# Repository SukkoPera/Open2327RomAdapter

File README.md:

# Open2327RomAdapter
Open2327RomAdapter is an Open Hardware adapter PCB that allows the use of a 27xxx EPROM in place of a 2364 and other PROMs. This is mainly useful for replacing the KERNAL and other ROMs in VIC-20 and Commodore 64 home computers and 1541 drives.

## Summary
The KERNAL ROM in a Commodore 64 is a 2364 model (8 KB), which comes in a 24-pin package. In some cases it is necessary to replace it, but 24-pin EPROMs are not easily available. Besides, in some cases you want to have multiple KERNAL ROMs that you can select with a switch (think about [JiffyDOS](http://www.go4retro.com/products/jiffydos/)).

Open2327RomAdapter comes as an adapter PCB that sits inbetween the original socket and the new chip and solves both those problems, by allowing the use of 28-pin EPROMs, which are cheaper and much more common. It also allows the use of EPROMs bigger than the original ROM, with solder pads where switches can be wired to allow the selection of a particular ROM.

## Assembly
1. Solder the R1-R3 0805 SMD resistors first (Note: do NOT install R4, see below). My suggested technique is as follows: put a small blob of solder on one of the pads, then grab a resistor with tweezers, reheat the solder and slide the resistor into it, keeping it flat on the board. Hold it in place with your tweezers and take the iron away. If you didn't place it straight, reheat and correct with the tweezers. Finally solder the other end. It's not that hard, you just need to practice a few times.
1. Put the pin headers into a solderless breadboard and lay the board on them, with the 0805 resistors facing down (i.e.: you should not see them). Make sure to use the two shortest hole series. Solder into place.
1. Remove the board from the solderless breadboard. Using flush cutters, cut the top two pins on the right (on the soldering side) so that they are as flush to the board as possible. Repeat with the bottom two pins. Take the socket and do a test fit, it should sit flush to the board.
1. Turn the board over and solder down the socket. Again, make sure it sits as flush as possible.
1. You are done! Try to fit the adapter in the socket on your board or solder it down, if you prefer. In both cases, you can trim the pins shorter if you need.

## Installation
Open2327RomAdapter has been designed with a Winbond W27C512 EEPROM in mind (and W27*E*512 should work just as well). This is a 64 KB chip (thus it can hold up to 8 ROM images, more than enough for most needs), which is widely available, cheap and electrically erasable, which avoids the need for a clunky UV-eraser. **This is the only part that was thoroughly tested**.

Three 0805 SMD resistors must be soldered to the bottom side of the board, according to the following table:

| (E)EPROM | Size  | # of images |  R1  |  R2  |  R3  | Switchable pads |
|----------|-------|-------------|------|------|------|-----------------|
| 2764     | 8 KB  | 1           | 0R   | 0R   | 0R   | -               |
| 27128    | 16 KB | 2           | 10k  | 0R   | 0R   | A13             |
| 27256    | 32 KB | 4           | 10k  | 10k  | 0R   | A13, A14        |
| 27512*   | 64 KB | 8           | 10k  | 10k  | 10k  | A13, A14, A15   |

\* This is the only configuration that has been tested. **USE OTHER CONFIGURATIONS AT YOUR RISK!**

Note that `0R` means that you have to install a 0-ohm resistor. Alternatively you can bridge the pads with a solder blob, but don't leave the spot empty. Where the recommended value is `10k`, instead, you have some flexibility: probably any value between 5k and 100k will do.

When flashing the (E)EPROM, make sure that every file is exactly 8192 bytes long and just concatenate them. You don't need to use all of the available space, but keep in mind that the unused address lines are pulled high. This means that if you use a 27512 EPROM with a single image and no switches, for instance, the image must be flashed at $E000 (i.e.: as if it was the last of 8 concatenated images).

The adapter has been carefully sized to fit both inside a VIC-20 (tested on the KERNAL and BASIC ROMs on an Assy #250403 board) C64 (tested on the KERNAL of an Assy #250425 board) and a 1541 drive. It can usually be installed in the original ROM socket, with no need to desolder it.

To switch between ROMs, you will need one or more switches. Every switch must connect one of the A13-A15 pads to ground when enabled. A ground pad is available on the board, but any ground spot on the C64 board can be used as well, if easier to reach. Since having more than switch can be cumbersome, a rotary switch can be used as well.

### Replacing 2332 ROMs
2332 ROMs only hold 4 Kb of data. This means that you can switch among even more ROM images if you use a bigger EPROM. In order to do this, you will need to free the A12 address line, which requires a few extra steps:
1. Solder a 10k resistor at R4.
1. Cut the JP1 jumper open.
1. Solder another switch between the A12 pad on the bottom of the board and ground.

**IMPORTANT: ALWAYS TURN YOUR C64 OFF BEFORE MOVING THE ROM SELECTION SWITCH(ES).**

## License
The Open2327RomAdapter documentation, including the design itself, is copyright &copy; SukkoPera 2017-2020.

Open2327RomAdapter is Open Hardware licensed under the [CERN OHL v. 1.2](http://ohwr.org/cernohl).

You may redistribute and modify this documentation under the terms of the CERN OHL v.1.2. This documentation is distributed *as is* and WITHOUT ANY EXPRESS OR IMPLIED WARRANTIES whatsoever with respect to its functionality, operability or use, including, without limitation, any implied warranties OF MERCHANTABILITY, SATISFACTORY QUALITY, FITNESS FOR A PARTICULAR PURPOSE or infringement. We expressly disclaim any liability whatsoever for any direct, indirect, consequential, incidental or special damages, including, without limitation, lost revenues, lost profits, losses resulting from business interruption or loss of data, regardless of the form of action or legal theory under which the liability may be asserted, even if advised of the possibility or likelihood of such damages.

A copy of the full license is included in file [LICENSE.pdf](LICENSE.pdf), please refer to it for applicable conditions. In order to properly deal with its terms, please see file [LICENSE_HOWTO.pdf](LICENSE_HOWTO.pdf).

The contact points for information about manufactured Products (see section 4.2) are listed in file [PRODUCT.md](PRODUCT.md).

Any modifications made by Licensees (see section 3.4.b) shall be recorded in file [CHANGES.md](CHANGES.md).

The Documentation Location of the original project is https://github.com/SukkoPera/Open2327RomAdapter/.

## Support the Project
If you want to support the project, you can order the boards from PCBWay through this link:

You get my gratitude and cheap, professionally-made and good quality PCBs, I get some credit that will help with this and [other projects](https://www.pcbway.com/project/member/shareproject/?bmbid=41100). You won't even have to worry about the various PCB options, it's all pre-configured for you!

Also, if you still have to register to that site, [you can use this link](https://www.pcbway.com/setinvite.aspx?inviteid=41100) to get some bonus initial credit (and yield me some more).

You can also buy me a coffee if you want:

## Get Support
If you need help or have questions, you can join [the official Telegram group](https://t.me/joinchat/HUHdWBC9J9JnYIrvTYfZmg).

## Thanks
The following links were useful during the development of this project:
- https://ist.uwaterloo.ca/~schepers/roms.html
- https://ist.uwaterloo.ca/~schepers/sockets.html
- http://smisioto.no-ip.org/elettronica/kicad/kicad.htm

The following people contributed work:
- Andre Miller helped with the testing.
- Tim Abraham suggested and tested the A12 hack.

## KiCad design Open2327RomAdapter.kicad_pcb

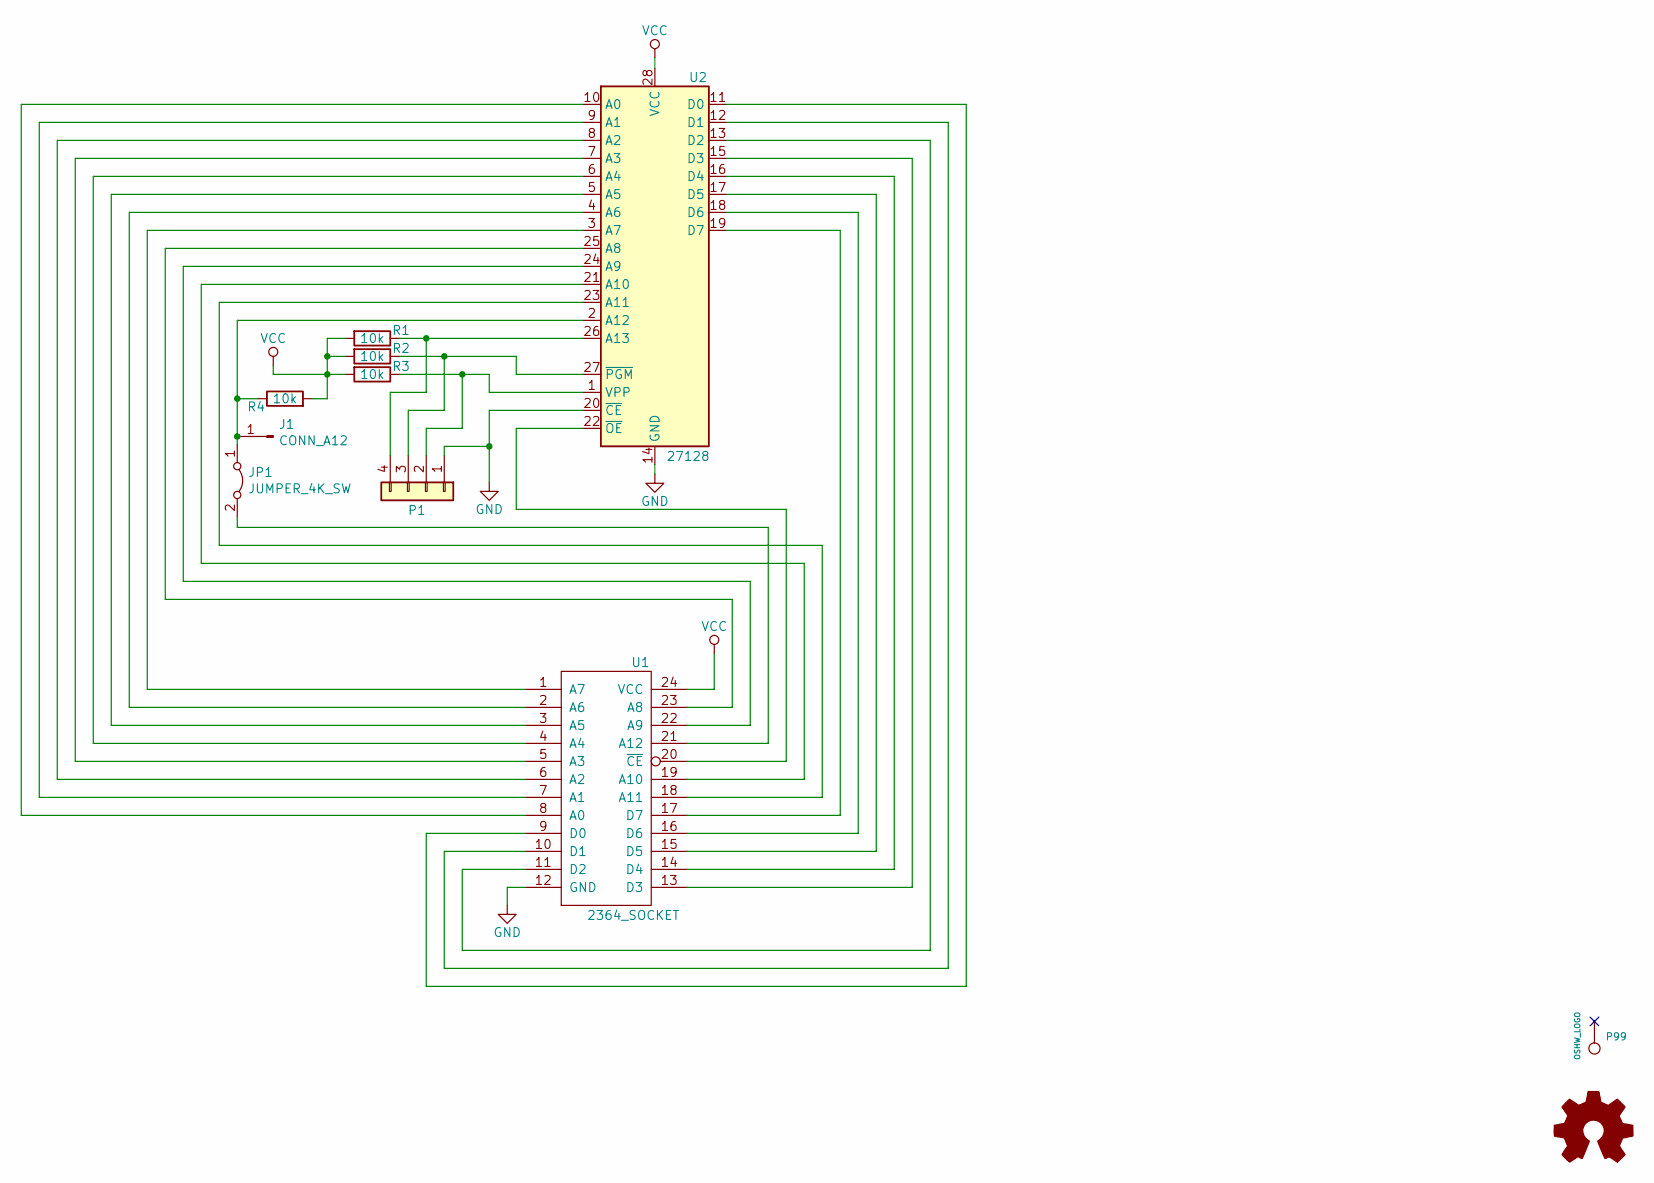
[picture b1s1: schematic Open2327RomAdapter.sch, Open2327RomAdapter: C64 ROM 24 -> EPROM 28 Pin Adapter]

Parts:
J1: CONN_A12; TestPoint_Pad_D1.0mm
JP1: JUMPER_4K_SW; SolderJumper-2_P1.3mm_Bridged_RoundedPad1.0x1.5mm
P1: Conn_01x04; Solderable_PinHeader_1x04
P99: OSHW_LOGO; OSHW-Logo2_7.3x6mm_Copper
R1, R2, R3, R4: 10k; R_0805_2012Metric_Pad1.15x1.40mm_HandSolder
U1: 2364_SOCKET; DIP-24_W15.24mm-Notch
U2: 27128; DIP-28_W15.24mm-Notch

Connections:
GND: P1.1, U1.12 (GND), U2.14 (GND), U2.20 (~CE)
unnamed: J1.1, JP1.1 (A), R4.1, U2.2 (A12)
unnamed: JP1.2 (B), U1.21 (A12)
unnamed: P1.2, R3.1, U2.1 (VPP)
unnamed: P1.3, R2.1, U2.27 (~PGM)
unnamed: P1.4, R1.1, U2.26 (A13)
unnamed: U1.1 (A7), U2.3 (A7)
unnamed: U1.2 (A6), U2.4 (A6)
unnamed: U1.3 (A5), U2.5 (A5)
unnamed: U1.4 (A4), U2.6 (A4)
unnamed: U1.5 (A3), U2.7 (A3)
unnamed: U1.6 (A2), U2.8 (A2)
unnamed: U1.7 (A1), U2.9 (A1)
unnamed: U1.8 (A0), U2.10 (A0)
unnamed: U1.9 (D0), U2.11 (D0)
unnamed: U1.10 (D1), U2.12 (D1)
unnamed: U1.11 (D2), U2.13 (D2)
unnamed: U1.13 (D3), U2.15 (D3)
unnamed: U1.14 (D4), U2.16 (D4)
unnamed: U1.15 (D5), U2.17 (D5)
unnamed: U1.16 (D6), U2.18 (D6)
unnamed: U1.17 (D7), U2.19 (D7)
unnamed: U1.18 (A11), U2.23 (A11)
unnamed: U1.19 (A10), U2.21 (A10)
unnamed: U1.20 (~CE), U2.22 (~OE)
unnamed: U1.22 (A9), U2.24 (A9)
unnamed: U1.23 (A8), U2.25 (A8)
VCC: R1.2, R2.2, R3.2, R4.2, U1.24 (VCC), U2.28 (VCC)

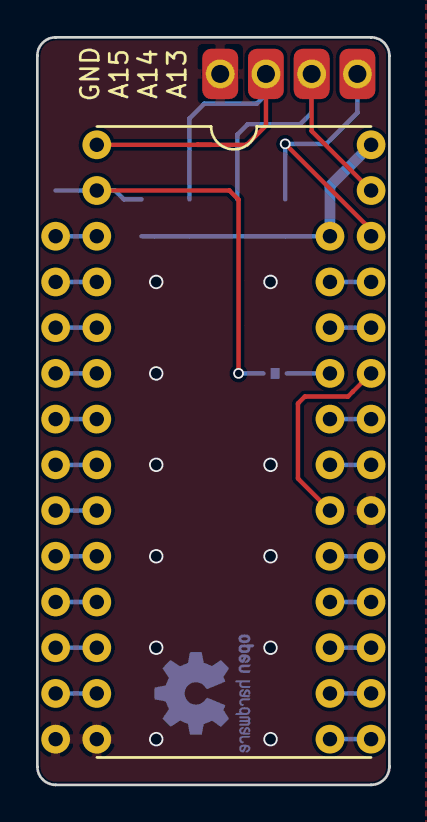
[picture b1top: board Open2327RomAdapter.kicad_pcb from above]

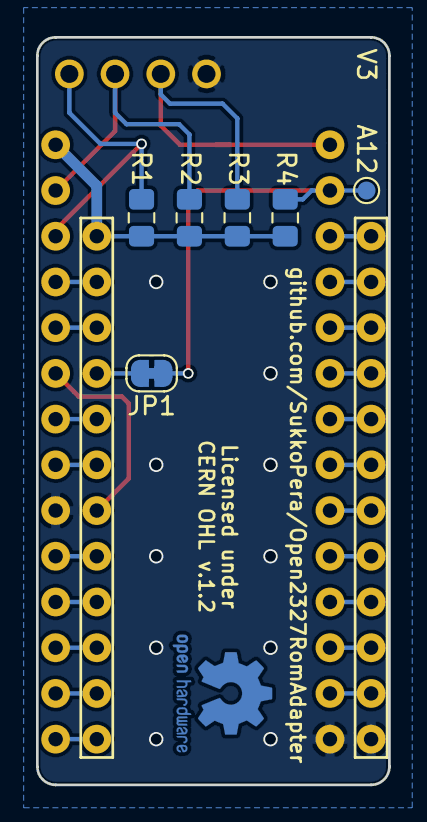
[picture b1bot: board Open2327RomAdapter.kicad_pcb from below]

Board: 2 copper layers, 19.6 x 41.5 mm, 10 parts (7 on the bottom side), 28 nets.

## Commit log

2017-09-27 Add pull-up resistors
2017-09-27 Remove backup file
2017-09-27 Move pull-up resistors to bottom of board
2017-09-27 Update board This should be the board that went to prototype production. It has been tested and is working great!
2017-09-27 Cleanup
2017-09-27 Add .gitignore
2017-10-10 Add docs
2017-10-10 Minor fixes
2017-11-08 Add assembly instructions
2017-12-30 Fix URL, better ground plane, round corners
2018-01-05 Final touches for V2
2019-05-05 Move solderable pads to 0.1" pitch and drill a hole through them Also port to Kicad 5 and use builtin components/footprints
2019-05-05 Update renders and schematic PDF
2019-05-05 Add license
2019-05-05 Mention license in README.md
2019-05-05 Add option to buy me a coffee :)
2019-05-05 Add P99 description
2019-05-05 Make corners more rounded
2019-05-05 Fix ERC
2019-08-26 Fix #2
2019-08-26 Add coffee
2019-08-26 Change note on W27E512
2020-04-23 Add jumper, pull-up and pad so that A12 can optionally be driven externally
2020-10-04 Add instructions about 2332 replacement
2020-10-04 Move renders to img directory
2020-10-04 Update renders
2020-10-04 Close #3
2020-10-04 Update schematics
2020-10-04 Update board link
2026-02-13 Change coffee donation link image in README
    Updated the 'Buy Me a Coffee' link with a new image.

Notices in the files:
Open2327RomAdapter.kicad_pcb:
Licensed under CERN OHL v.1.2
